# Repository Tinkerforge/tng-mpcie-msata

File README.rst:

TNG MPCIE MSATA
===============

TBD

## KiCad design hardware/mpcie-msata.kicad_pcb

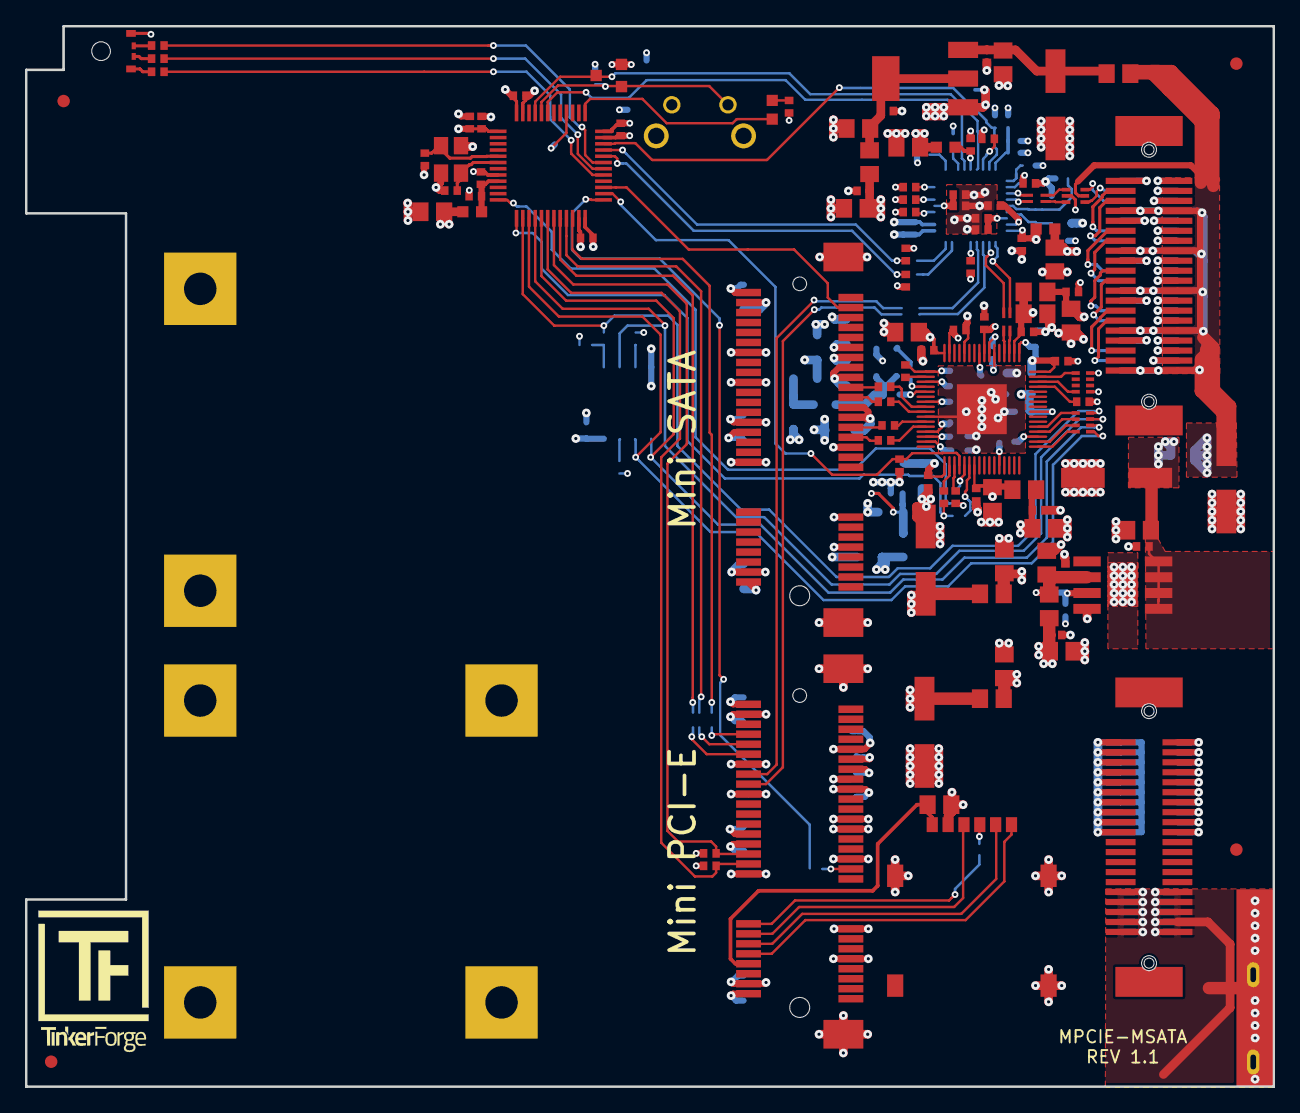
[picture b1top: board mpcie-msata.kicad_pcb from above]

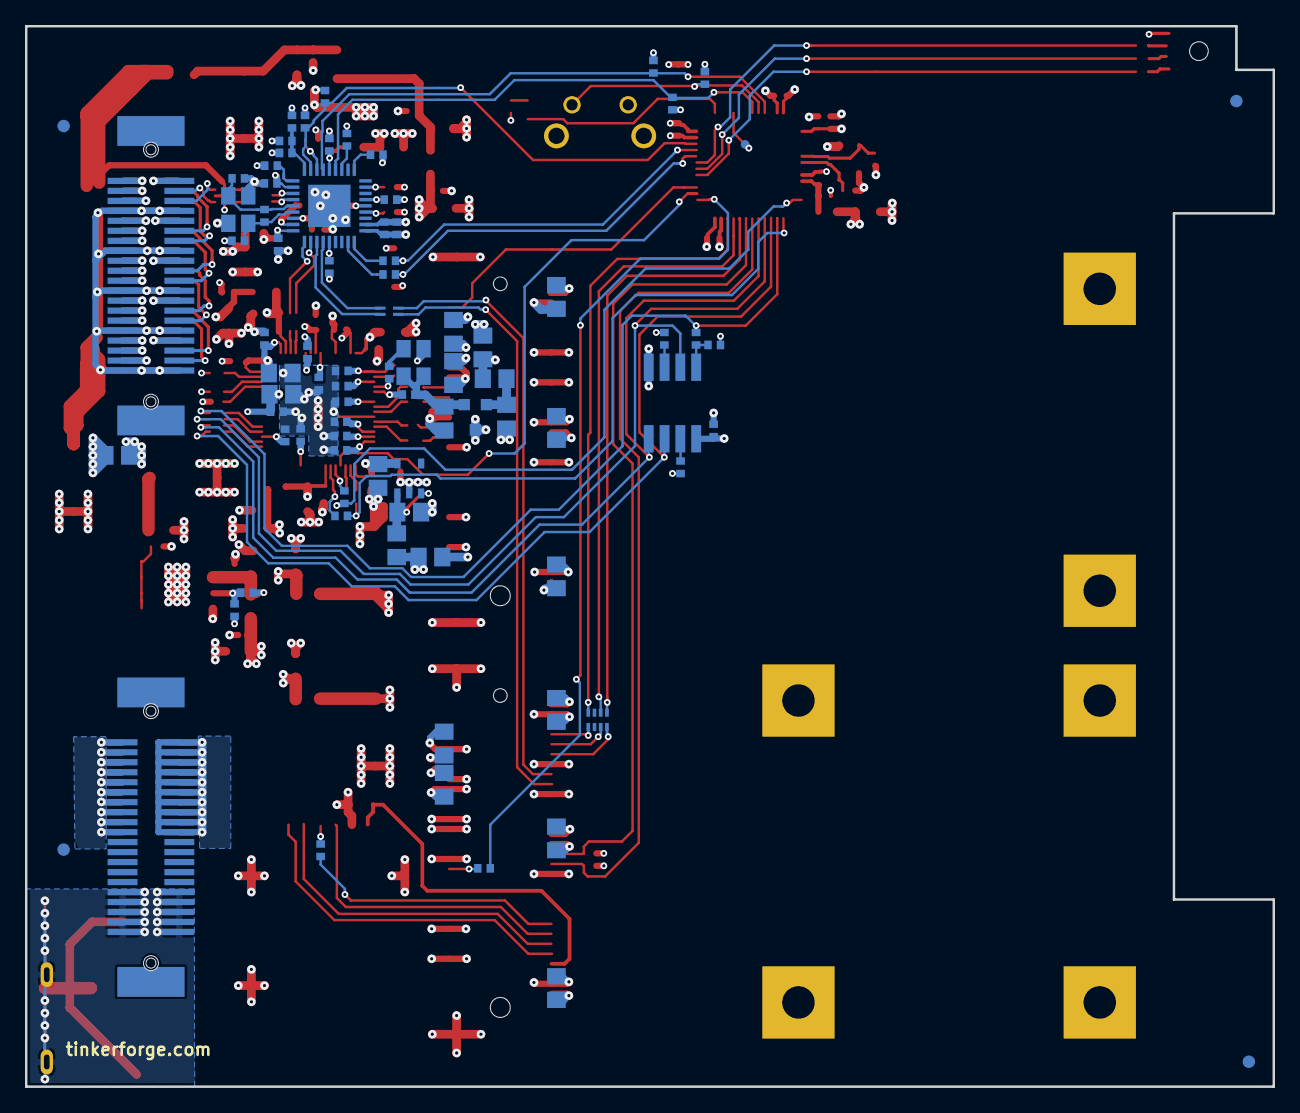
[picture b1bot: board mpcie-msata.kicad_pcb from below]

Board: 4 copper layers, 100.0 x 85.0 mm, 194 parts (84 on the bottom side), 128 nets.

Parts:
C101, C102, C137, C138: 33pF; C0402F
C103, C104, C105, C106, C107, C110, C112, C114, C117, C127, C129, C130, C131, C133, C308, C314, C315, C316, C317, C318, C319, C320, C321, C322, C323, C324, C332, C333, C334, C335, C336, C337, C338, C343, C344, C347: 100nF; C0402F
C108, C109, C111, C113, C115, C118, C119, C120, C123, C124, C134, C135, C141, C142, C143, C144: 1uF; C0402F
C116, C125, C128, C132, C136, C139, C140, C146, C147, C201, C203, C204, C205, C206, C207, C209, C301, C302, C303, C304, C305, C309, C325, C326, C327, C328, C329, C330, C331, C339, C340, C341, C342, C345, C346: 10uF; C0805E
C121, C122: 47pF; C0402F
C126: 1nF; C0402F
C148, C150, C151, C202, C306: 100uF; ELKO_63
C310, C311, C312, C313: 10nF; C0402F
D102: blue; D0603F
Fiducial_Mark: VAL**; Fiducial_Mark
Fiducial_Mark#2, Fiducial_Mark#3, Fiducial_Mark#4, Fiducial_Mark#5, Fiducial_Mark#6, Fiducial_Mark#7, Fiducial_Mark#8: VAL**; Fiducial_Mark
J102: TNG-Power-BTM; TNG-40-BTM
J103: TNG-Power-TOP; TNG-40-TOP
J104: TNG-Data-BTM; TNG-40-BTM
J105: TNG-Data-TOP; TNG-40-TOP
J201: Mini-PCIE
J202: SIM8060
J301: Mini-SATA
L101, L103, L108: FB; R0603F
L102, L105, L109: 744230900; WE-CNSW-0603
L106, L107, L111, L112, L201, L301, L302, L303, L304, L305: INDUCTs; R0805E
LED101: EASV3015RGBA0; LED-RGB-LP
P101: Debug; DEBUG_PAD
P102: PE; PE_Hook
Q101: 2N7002; SOT23GDS
Q301: 40MHz; CRYSTAL_3225_4
R101, R102, R104, R105, R106, R108, R109, R111, R116, R306, R307, R308, R311, R312: 10k; R0402F
R103: 1M; R0402F
R110: 12k; R0402F
R112, R113: 22; R0402F
R114, R121, R201, R202, R203: 1k; R0402F
R115, R119, R301, R310: 0; R0402F
R118, R204, R302, R303, R304, R305, R309, R313: DNP; R0402F
R120: 56; R0402F
R122: 100k; R0402F
R123: 169k; R0402F
R124: 30.1k; R0402F
RP201, RP301: 1k; 4X0402
RP302: 100; 4X0402
SW101: BOOT; TACT-6MM-HOR
U101: USB2514B; QFN36-6x6mm-0.5mm
U102: LD1117; SOT-223
U103: TPS7A7002; SO-8-EP
U104: STM32F070CBT6; LQFP48
U105: 82400152; SOT563-SPEC
U301: TUSB9261PVP; QFP-64_7x7_Pitch0.4mm
U302: TLV71211DBVR; SOT23-5
U303: AP7333-18SAG-7; SOT23-3
U304: AT25DF011-SSHN-T; SO-8
X101: 24MHz; CRYSTAL_3225
X102: 8MHz; CRYSTAL_3225

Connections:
1V8: C308.1, C326.1, Q301.1, Q301.4, U303.2
3V3: C116.1, C123.1, C125.1, C127.1, C128.1, C129.1, C130.1, C131.1, C134.1, C139.1, C347.2, L101.1, L103.1, L106.1, L108.1, LED101.1, R101.2, R102.2, R104.2, R105.2, R106.2, R108.2, R111.2, R116.1, R121.2, R122.1, R311.1, R312.1, R313.2, SW101.1, U104.1, U104.24, U104.36, U104.48, U304.8
3V3-MPCIE: C201.1, C202.1, C203.2, C204.2, C205.2, C206.2, J201.2, J201.24, J201.39, J201.41, J201.52, L201.2, R203.1
3V3-MSATA: C301.2, C302.2, C303.2, C304.2, C305.2, C306.1, J301.2, J301.24, J301.39, J301.41, J301.52, L301.2
5V-STACK: C151.1, J104.7, J104.8, J104.15, J104.16, J104.23, J104.24, J104.31, J104.32, J104.39, J104.40, J105.7, J105.8, J105.15, J105.16, J105.23, J105.24, J105.31, J105.32, J105.39, J105.40, L111.1, L112.1, U105.5
+1.1V: C314.2, C315.2, C316.2, C317.2, C318.2, C319.2, C320.2, C321.2, C322.2, C323.2, C324.2, C325.1, C327.1, R307.2, U301.1, U301.12, U301.19, U301.32, U301.33, U301.41, U301.47, U301.49, U301.55, U301.61, U301.63, U302.5
+3.3VP: C132.1, C135.1, C209.2, C309.2, C330.1, C331.1, C343.2, C344.2, C345.1, C346.1, L107.1, L201.1, L301.1, L302.1, L303.1, L304.1, L305.1
BOOT: Q101.G, R114.2, SW101.2, U104.44
Earth: J102.31, J102.32, J102.33, J102.34, J102.35, J102.36, J102.37, J102.38, J102.39, J102.40, J103.31, J103.32, J103.33, J103.34, J103.35, J103.36, J103.37, J103.38, J103.39, J103.40, P102.1
GND: C101.2, C102.2, C103.2, C104.2, C105.2, C106.2, C107.2, C108.2, C109.2, C110.2, C111.2, C112.2, C113.2, C114.2, C115.2, C116.2, C117.2, C118.2, C119.2, C120.2, C121.2, C122.2, C123.2, C124.2, C125.2, C126.2, C127.2, C128.2, C129.2, C130.2, C131.2, C132.2, C133.2, C134.2, C135.2, C136.2, C137.1, C138.1, C139.2, C140.2, C141.2, C142.2, C143.2, C144.2, C146.2, C147.2, C148.2, C150.2, C151.2, C201.2, C202.2, C203.1, C204.1, C205.1, C206.1, C207.2, C209.1, C301.1, C302.1, C303.1, C304.1, C305.1, C306.2, C309.1, C314.1, C315.1, C316.1, C317.1, C318.1, C319.1, C320.1, C321.1, C322.1, C323.1, C324.1, C325.2, C326.2, C327.2, C328.2, C329.2, C330.2, C331.2, C332.1, C333.1, C334.1, C335.1, C336.1, C337.1, C338.1, C339.2, C340.2, C341.2, C342.2, C343.1, C344.1, C345.2, C346.2, C347.1, J104.1, J104.2, J104.3, J104.5, J104.9, J104.10, J104.11, J104.13, J104.17, J104.18, J104.19, J104.21, J104.25, J104.26, J104.27, J104.29, J104.33, J104.34, J104.35, J104.37, J105.1, J105.2, J105.4, J105.6, J105.9, J105.10, J105.12, J105.14, J105.17, J105.18, J105.20, J105.22, J105.25, J105.26, J105.28, J105.30, J105.33, J105.34, J105.36, J105.38, J201.4, J201.9, J201.15, J201.18, J201.21, J201.26, J201.27, J201.29, J201.34, J201.35, J201.37, J201.40, J201.43, J201.50, J201.MNT, J202.5, J301.4, J301.9, J301.15, J301.18, J301.21, J301.26, J301.27, J301.29, J301.34, J301.35, J301.37, J301.40, J301.50, J301.MNT, Q101.S, R109.2, R110.1, R114.1, R118.2, R124.2, R202.2, R306.1, R309.1, U101.11, U101.EXP, U102.1, U103.8, U103.EP, U104.8, U104.23, U104.35, U104.47, U105.2, U301.44, U301.58, U301.EP, U302.2, U303.3, U304.4, X101.3, X102.3
LDO-IN: C143.1, C146.1, C148.1, L111.2, U103.1, U103.2, U103.3, U103.4
LEDB: R120.1, U104.31
LEDG: R119.1, U104.30
LEDR: R115.1, U104.29
MPCIE_#DISABLE: J201.20, R202.1, U104.18
MPCIE_#RESET: J201.22, R203.2, U104.19
MPCIE_DM: J201.36, L102.3
MPCIE_DP: J201.38, L102.2
MPCIE_LED_WIFI: RP201.2, U104.21
MPCIE_LED_WPAN: RP201.4, U104.22
MPCIE_LED_WWAN: RP201.1, U104.20
MPCIE_PPS: R201.2, U104.25
MSATA_ACTIVITY_LED: J301.49, U104.27
MSATA_DM: L105.4, U301.35
MSATA_DP: L105.1, U301.36
MSATA_EN: R306.2, U104.26, U301.4
MSATA_RX: R302.2, R304.2, U104.12
MSATA_SPI_CLK: RP302.1, U104.15, U304.6
MSATA_SPI_CS: R310.2, RP302.4, U104.14
MSATA_SPI_DI: RP302.3, U104.16, U304.2
MSATA_SPI_DO: RP302.2, U104.17, U304.5
MSATA_TX: R303.2, R305.2, U104.13
unnamed: C101.1, R103.2, U101.32, X101.1
unnamed: C102.1, R103.1, U101.33, X101.2
unnamed: C103.1, C106.1, C111.1, C113.1, L101.2, U101.15, U101.23
unnamed: C104.1, C108.1, U101.34
unnamed: C105.1, C109.1, U101.14
unnamed: C107.1, C110.1, C112.1, C114.1, C115.1, C118.1, C119.1, C120.1, L103.2, U101.5, U101.10, U101.29, U101.36
unnamed: C124.1, C133.1, L108.2, U104.9
unnamed: C126.1, R118.1, R122.2, U101.27
unnamed: C136.1, C141.1, L106.2, U102.2
unnamed: C137.2, U104.5, X102.2
unnamed: C138.2, U104.6, X102.1
unnamed: C140.1, C142.1, L107.2, R123.1, U103.6
unnamed: C144.1, C147.1, C150.1, L112.2, U102.3
unnamed: C207.1, J201.8, J202.1
unnamed: C308.2, Q301.2, U301.53
unnamed: C310.1, U301.56
unnamed: C310.2, J301.33
unnamed: C311.1, U301.57
unnamed: C311.2, J301.31
unnamed: C312.1, U301.59
unnamed: C312.2, J301.25
unnamed: C313.1, U301.60
unnamed: C313.2, J301.23
unnamed: C328.1, L302.2, U302.1, U302.3
unnamed: C329.1, L303.2, U303.1
unnamed: D102.1, R121.1
unnamed: D102.2, U104.37
unnamed: J104.4, U105.4
unnamed: J104.6, U105.6
unnamed: J104.12, J105.3
unnamed: J104.14, J105.5
unnamed: J104.20, J105.11
unnamed: J104.22, J105.13
unnamed: J104.28, J105.19
unnamed: J104.30, J105.21
unnamed: J104.36, J105.27
unnamed: J104.38, J105.29
unnamed: J201.10, J202.7
unnamed: J201.12, J202.3
unnamed: J201.14, J202.2
unnamed: J201.16, R204.2
unnamed: J201.19, R201.1
unnamed: J201.42, RP201.8
unnamed: J201.44, RP201.7
unnamed: J201.46, RP201.5
unnamed: J202.6, R204.1
unnamed: L102.1, U101.4
unnamed: L102.4, U101.3
unnamed: L105.2, U101.2
unnamed: L105.3, U101.1
unnamed: L109.1, U105.3
unnamed: L109.4, U105.1
unnamed: LED101.2, R120.2
unnamed: LED101.3, R119.2
unnamed: LED101.4, R115.2
unnamed: P101.1, U104.40
unnamed: Q301.3, R301.2
unnamed: R101.1, U101.28
unnamed: R102.1, U101.13
unnamed: R104.1, U101.17
unnamed: R105.1, U101.19
unnamed: R108.1, U101.21
unnamed: R109.1, U101.25
unnamed: R110.2, U101.35
unnamed: R112.1, U101.9
unnamed: R113.1, U101.8
unnamed: R123.2, R124.1, U103.7
unnamed: R301.1, U301.52
unnamed: R302.1, U301.3
unnamed: R303.1, U301.2
unnamed: R304.1, U301.5
unnamed: R305.1, U301.6
unnamed: R307.1, U301.50
unnamed: R308.1, U301.39
unnamed: R308.2, U301.38
unnamed: R309.2, U301.29
unnamed: R310.1, R313.1, U304.1
unnamed: R311.2, U304.3
unnamed: R312.2, U304.7
unnamed: RP301.5, U301.31
unnamed: RP301.8, U301.30
unnamed: RP302.5, U301.21
unnamed: RP302.6, U301.20
unnamed: RP302.7, U301.18
unnamed: RP302.8, U301.17
PWR-GND: J102.1, J102.3, J102.5, J102.7, J102.9, J102.11, J102.13, J102.15, J102.17, J102.19, J103.2, J103.4, J103.6, J103.8, J103.10, J103.12, J103.14, J103.16, J103.18, J103.20
PWR-VCC: J102.2, J102.4, J102.6, J102.8, J102.10, J102.12, J102.14, J102.16, J102.18, J102.20, J103.1, J103.3, J103.5, J103.7, J103.9, J103.11, J103.13, J103.15, J103.17, J103.19
STM_USB_DM: C121.1, R113.2, U104.32
STM_USB_DP: C122.1, R112.2, U104.33
UP_USB_DM: L109.3, U101.30
UP_USB_DP: L109.2, U101.31
USB_RESET: C117.1, R116.2, U101.26, U104.34
USB_SMB_CLK: Q101.D, R111.1, U101.24, U104.45
USB_SMB_DATA: R106.1, U101.22, U104.43
VDDA_3P3V: C332.2, C334.2, C336.2, C338.2, C340.1, C342.1, L305.2, U301.34, U301.40, U301.48, U301.62
VDD_3P3V: C333.2, C335.2, C337.2, C339.1, C341.1, L304.2, RP301.1, RP301.4, U301.7, U301.24, U301.51

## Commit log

2020-01-08 add readme file
2020-02-13 copy project
2020-02-24 schematic improved
2020-02-25 schematic nearly finished
2020-02-26 fix schematic first placement
2020-02-28 placement nearly finished
2020-02-28 nearly completely routed
2020-03-02 routing improvement
2020-03-02 small update
2020-03-02 add fiducials
2020-03-02 add clamp
2020-05-14 fix values
2020-06-22 add hints
2020-06-22 add missing files
2020-09-04 add version 1.1
    * fix footprints
    * remove lm813
2020-09-07 fix footprints
2020-09-07 fix name
2020-09-08 fix names
2020-09-08 all footprints updated
2020-09-10 fix 3d stuff

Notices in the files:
hardware/mpcie-msata.kicad_pcb:
Licensed under CERN OHL v.1.1
Copyright (©) 2020, B.Nordmeyer
Copyright Tinkerforge GmbH 2020.
This documentation describes Open Hardware and is licensed under the
CERN OHL v. 1.1.
